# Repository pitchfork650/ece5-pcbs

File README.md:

# speakerpcb
speakerpcb for ece5

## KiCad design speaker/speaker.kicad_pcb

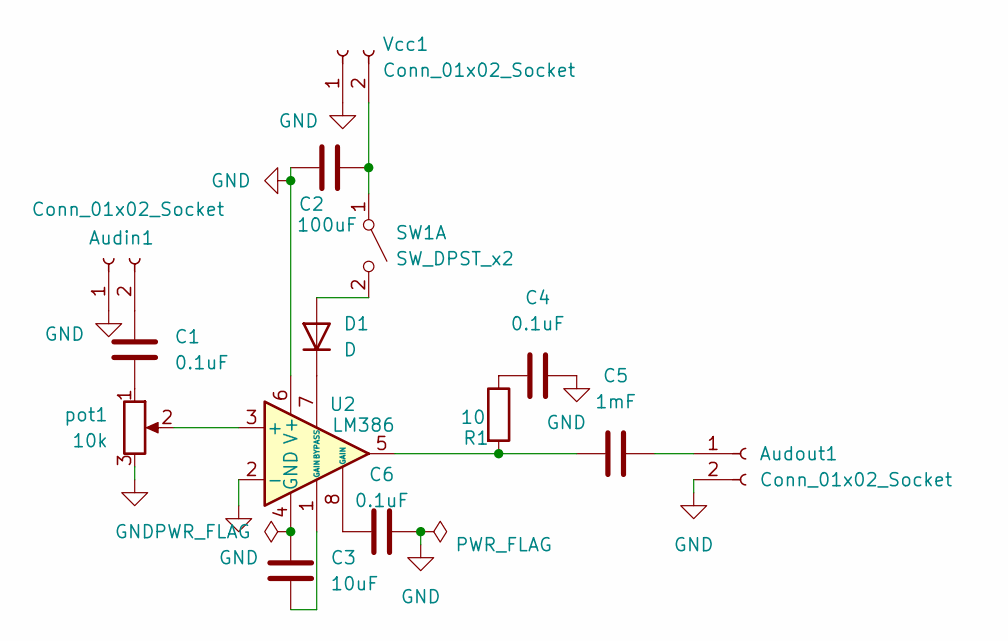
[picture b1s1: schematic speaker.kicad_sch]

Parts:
Audin1: Conn_01x02_Socket; PinSocket_1x02_P2.54mm_Vertical
Audout1: Conn_01x02_Socket; PinSocket_1x02_P2.54mm_Vertical
C1, C4, C6: 0.1uF; C_Disc_D3.0mm_W1.6mm_P2.50mm
C2: 100uF; CP_Radial_D6.3mm_P2.50mm
C3: 10uF; CP_Radial_D6.3mm_P2.50mm
C5: 1mF; CP_Radial_D10.0mm_P5.00mm
D1: D; D_A-405_P10.16mm_Horizontal
R1: 10; R_Axial_DIN0207_L6.3mm_D2.5mm_P10.16mm_Horizontal
SW1: SW_DPST_x2; PinSocket_1x02_P2.54mm_Vertical
U2: LM386; DIP-8_W10.16mm_LongPads
Vcc1: Conn_01x02_Socket; PinSocket_1x02_P2.54mm_Vertical
pot1: 10k; FanPinHeader_1x03_P2.54mm_Vertical

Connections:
GND: Audin1.1, Audout1.2, C2.1, C4.2, C6.1, U2.2 (-), U2.6 (V+), Vcc1.1, pot1.3
unnamed: Audin1.2, C1.1
unnamed: Audout1.1, C5.1
unnamed: C1.2, pot1.1
unnamed: C3.2, U2.1 (GAIN)
unnamed: C4.1, R1.1
unnamed: C5.2, R1.2, U2.5
unnamed: C6.2, U2.8 (GAIN)
unnamed: D1.2 (A), SW1.2 (B)
unnamed: D1.1 (K), U2.7 (BYPASS)
unnamed: C2.2, SW1.1 (A), Vcc1.2
unnamed: U2.3 (+), pot1.2
unnamed: C3.1, U2.4 (GND)

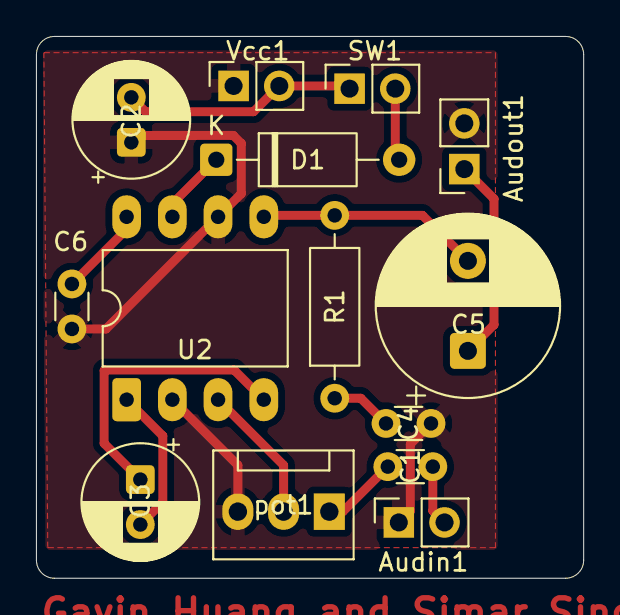
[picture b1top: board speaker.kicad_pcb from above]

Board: 2 copper layers, 30.4 x 30.1 mm, 14 parts (0 on the bottom side), 13 nets.
